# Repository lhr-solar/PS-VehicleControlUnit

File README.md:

# VehicleControlUnit
Vehicle Control Unit (VCU) for the 2026 Longhorn Racing Solar car

## Getting Started

### Cloning
Clone this repository using the following command
``` sh
git clone git@github.com:lhr-solar/PS-VehicleControlUnit.git --recursive
```

### Installation
Follow the installation instructions for your specific platform, found [here](https://lhrsolar.org/Embedded-Sharepoint/Installation/).  

Additionally, install the [Arduino IDE](https://docs.arduino.cc/software/ide/)

## Command Usage

### Firmware build and flash

Firmware builds use [Embedded-Sharepoint](Firmware/Embedded-Sharepoint) from `Firmware/Makefile`. Enter the nix shell first, then run all commands from `Firmware/`.

By default, **`FIRMWARE_TYPE=app`**: the image is linked for the resident UART bootloader (application region at `0x08010000`, 512 KB part with 64 KB bootloader). Full protocol, one-time bootloader programming, and host scripts: [UART Bootloader](Firmware/Embedded-Sharepoint/docs/UartBootloader.md). USART3 on PC10/PC11 matches the default bootloader UART on STM32G473.

**Nix shell (repository root):**

```sh
chmod +x ./run_nix.sh   # first time only
./run_nix.sh
cd Firmware
```

**Clean** (removes both `Firmware/build` and `Firmware/build/app`):

```sh
make clean
```

**Bootloader application (default)** — output under `Firmware/build/app`:

```sh
make
make flash
make flash-uart
```

**Standalone firmware** at `0x08000000` (no resident bootloader) — output under `Firmware/build`:

```sh
make clean
make FIRMWARE_TYPE=firmware
make flash FIRMWARE_TYPE=firmware
make flash-uart FIRMWARE_TYPE=firmware
```

When switching between `app` and `firmware`, run **`make clean`** first so linker maps and objects stay consistent.

**Other makefile variables:**

```sh
make PROJECT_TARGET=stm32g473xx    # default; override if you change MCU port
make NODAWG=1                      # optional macro for this repo
```

### Compiling tests

Tests live in `Firmware/tests/` and must be named `test_<name>.c`; the `test_` prefix and `.c` suffix are omitted from `TEST`.

```sh
make TEST=<name>
```

Example (`Firmware/tests/blinky_test.c`):

```sh
make TEST=blinky
make flash
```

To build a test image as standalone instead of the default bootloader app:

```sh
make clean
make TEST=blinky FIRMWARE_TYPE=firmware
make flash FIRMWARE_TYPE=firmware
```

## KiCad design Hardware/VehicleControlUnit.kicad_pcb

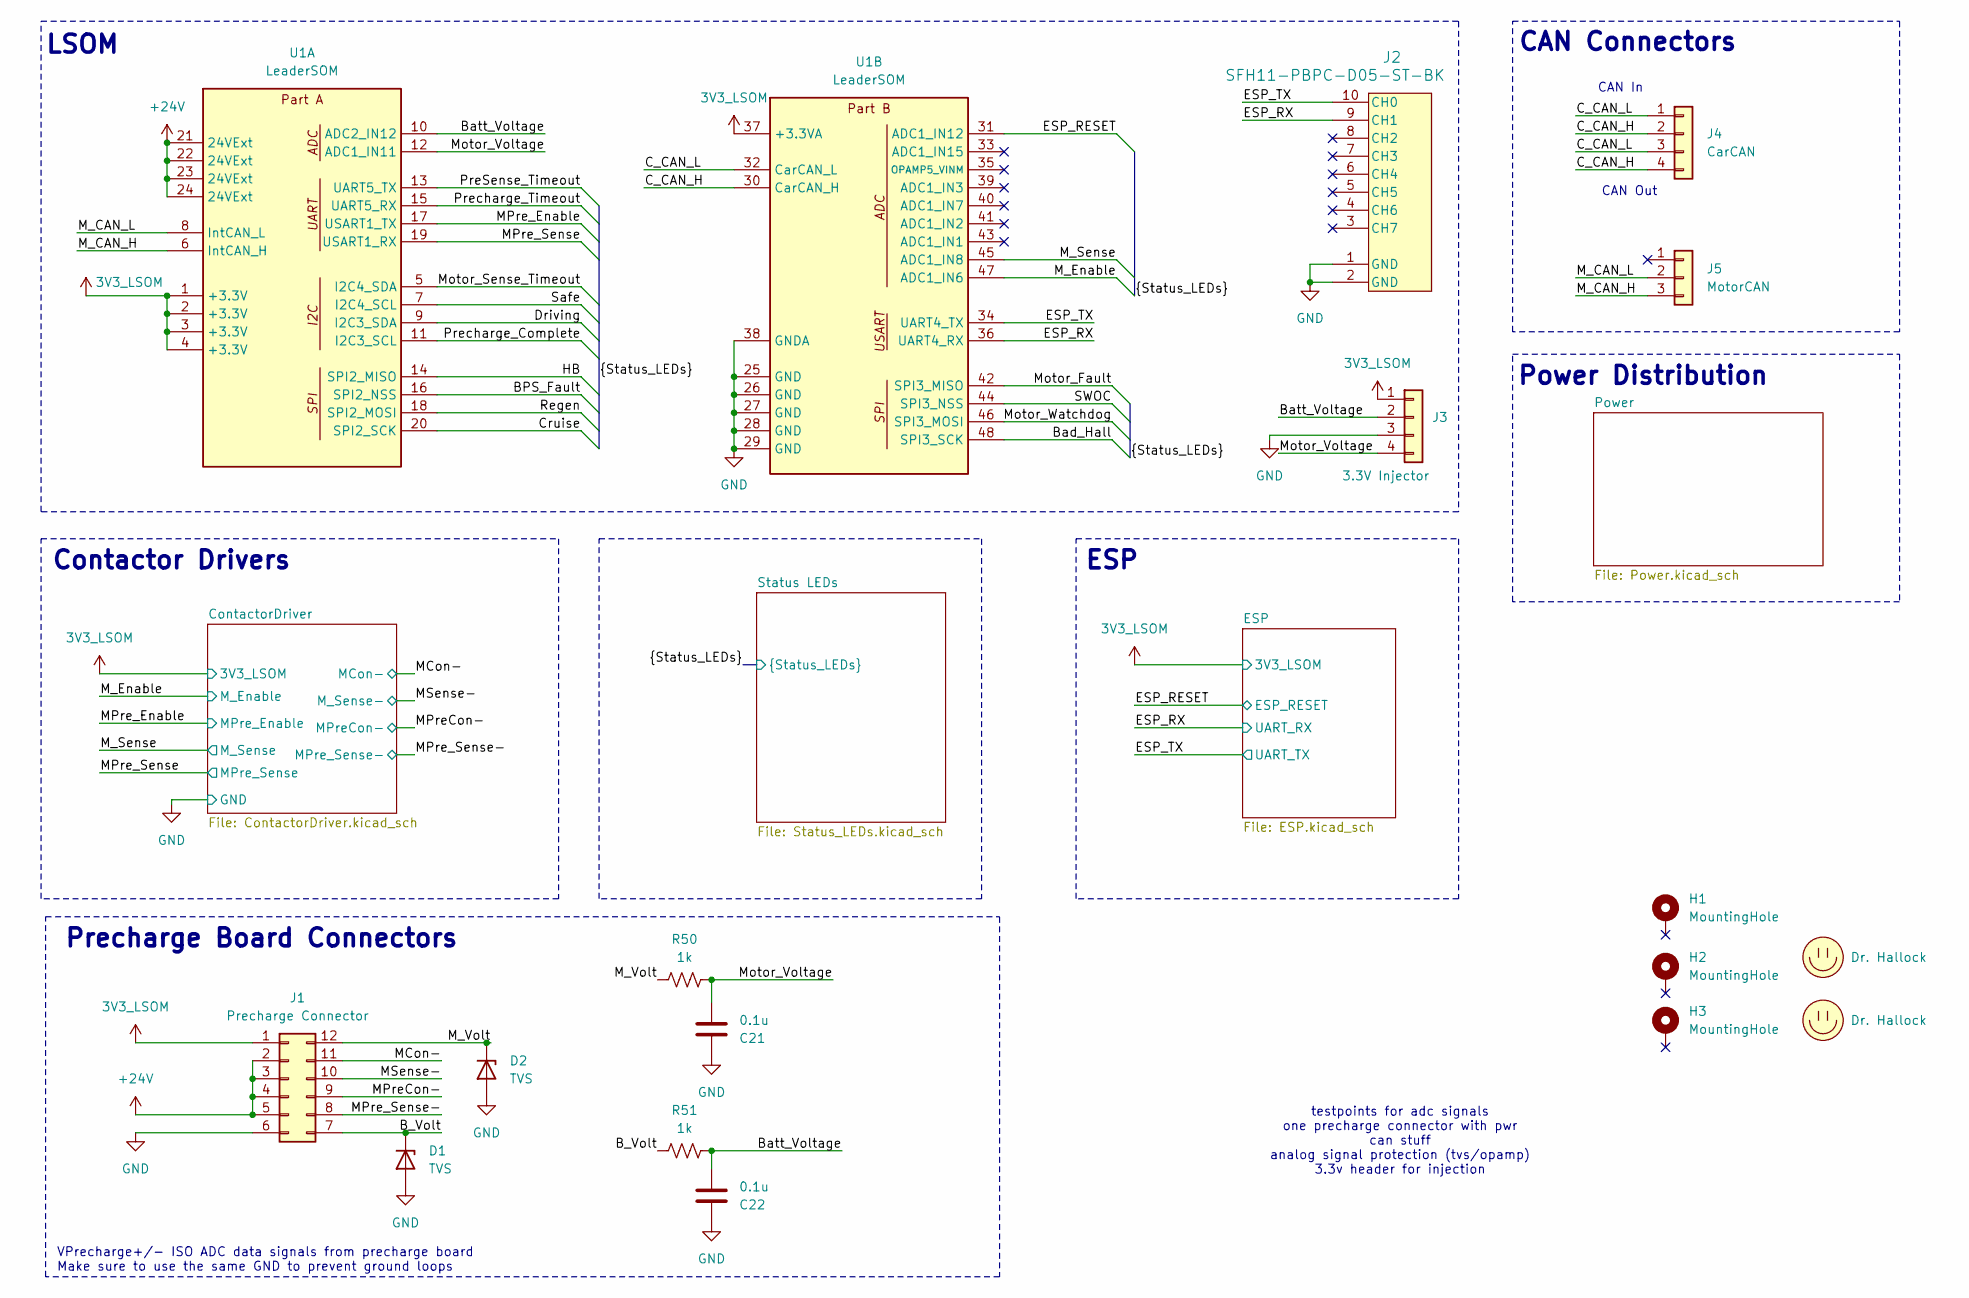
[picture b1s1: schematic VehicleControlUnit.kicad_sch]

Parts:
C21, C22: 0.1u; C_0603_1608Metric_Pad1.08x0.95mm_HandSolder; Mouser Part Number 963-HMK107B7104KA-T
D1, D2: TVS; D_SOD-123F; Mouser Part Number 576-SMF3.3
H1, H2, H3: MountingHole; MountingHole_3.2mm_M3_Pad_TopBottom
J1: Precharge Connector; Molex_Nano-Fit_105310-xx12_2x06_P2.50mm_Vertical; Mouser Part Number 538-105310-1112
J2: SFH11-PBPC-D05-ST-BK; CONN_SFH11-xxxC-D05-ST-XX_SUL
J3: 3.3V Injector; PinHeader_1x04_P2.54mm_Vertical
J4: CarCAN; Molex_Nano-Fit_105309-xx04_1x04_P2.50mm_Vertical; Mouser Part Number 538-105309-1104
J5: MotorCAN; Molex_Nano-Fit_105309-xx03_1x03_P2.50mm_Vertical; Mouser Part Number 538-105309-1103
LOGO1: Dr. Hallock; Hallock_Image_Tiny
LOGO2: Dr. Hallock; LHRs_LOGO
R50, R51: 1k; R_0603_1608Metric_Pad0.98x0.95mm_HandSolder; Mouser Part Number 71-CRCW06031K00FKEI
U1: LeaderSOM

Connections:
3V3_LSOM: J1.1, J3.1, U1.1 (+3.3V), U1.2 (+3.3V), U1.3 (+3.3V), U1.4 (+3.3V), U1.37 (+3.3VA); also elsewhere on the board
+24V: J1.2, J1.3, J1.4, J1.5, U1.21 (24VExt), U1.22 (24VExt), U1.23 (24VExt), U1.24 (24VExt); also elsewhere on the board
/BPS_Fault: U1.16 (SPI2_NSS); also elsewhere on the board
/B_Volt: D1.1 (K), J1.7, R51.2
/Bad_Hall: U1.48 (SPI3_SCK); also elsewhere on the board
/Batt_Voltage: C22.2, J3.2, R51.1, U1.10 (ADC2_IN12)
/C_CAN_H: J4.2, J4.4, U1.30 (CarCAN_H)
/C_CAN_L: J4.1, J4.3, U1.32 (CarCAN_L)
/Cruise: U1.20 (SPI2_SCK); also elsewhere on the board
/Driving: U1.9 (I2C3_SDA); also elsewhere on the board
/ESP_RESET: U1.31 (ADC1_IN12); also elsewhere on the board
/ESP_RX: J2.9 (CH1), U1.36 (UART4_RX); also elsewhere on the board
/ESP_TX: J2.10 (CH0), U1.34 (UART4_TX); also elsewhere on the board
/HB: U1.14 (SPI2_MISO); also elsewhere on the board
/MCon-: J1.11; also elsewhere on the board
/MPreCon-: J1.9; also elsewhere on the board
/MPre_Enable: U1.17 (USART1_TX); also elsewhere on the board
/MPre_Sense: U1.19 (USART1_RX); also elsewhere on the board
/MPre_Sense-: J1.8; also elsewhere on the board
/MSense-: J1.10; also elsewhere on the board
/M_CAN_H: J5.3, U1.6 (IntCAN_H)
/M_CAN_L: J5.2, U1.8 (IntCAN_L)
/M_Enable: U1.47 (ADC1_IN6); also elsewhere on the board
/M_Sense: U1.45 (ADC1_IN8); also elsewhere on the board
/M_Volt: D2.1 (K), J1.12, R50.2
/Motor_Fault: U1.42 (SPI3_MISO); also elsewhere on the board
/Motor_Sense_Timeout: U1.5 (I2C4_SDA); also elsewhere on the board
/Motor_Voltage: C21.2, J3.4, R50.1, U1.12 (ADC1_IN11)
/Motor_Watchdog: U1.46 (SPI3_MOSI); also elsewhere on the board
/PreSense_Timeout: U1.13 (UART5_TX); also elsewhere on the board
/Precharge_Complete: U1.11 (I2C3_SCL); also elsewhere on the board
/Precharge_Timeout: U1.15 (UART5_RX); also elsewhere on the board
/Regen: U1.18 (SPI2_MOSI); also elsewhere on the board
/SWOC: U1.44 (SPI3_NSS); also elsewhere on the board
/Safe: U1.7 (I2C4_SCL); also elsewhere on the board
GND: C21.1, C22.1, D1.2 (A), D2.2 (A), J1.6, J2.1 (GND), J2.2 (GND), J3.3, U1.25 (GND), U1.26 (GND), U1.27 (GND), U1.28 (GND), U1.29 (GND), U1.38 (GNDA); also elsewhere on the board

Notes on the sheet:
Precharge Board Connectors
CAN In
Contactor Drivers
testpoints for adc signals one precharge connector with pwr can stuff analog signal protection (tvs/opamp) 3.3v header for injection
Power Distribution
VPrecharge+/- ISO ADC data signals from precharge board Make sure to use the same GND to prevent ground loops
LSOM
ESP
CAN Out
CAN Connectors

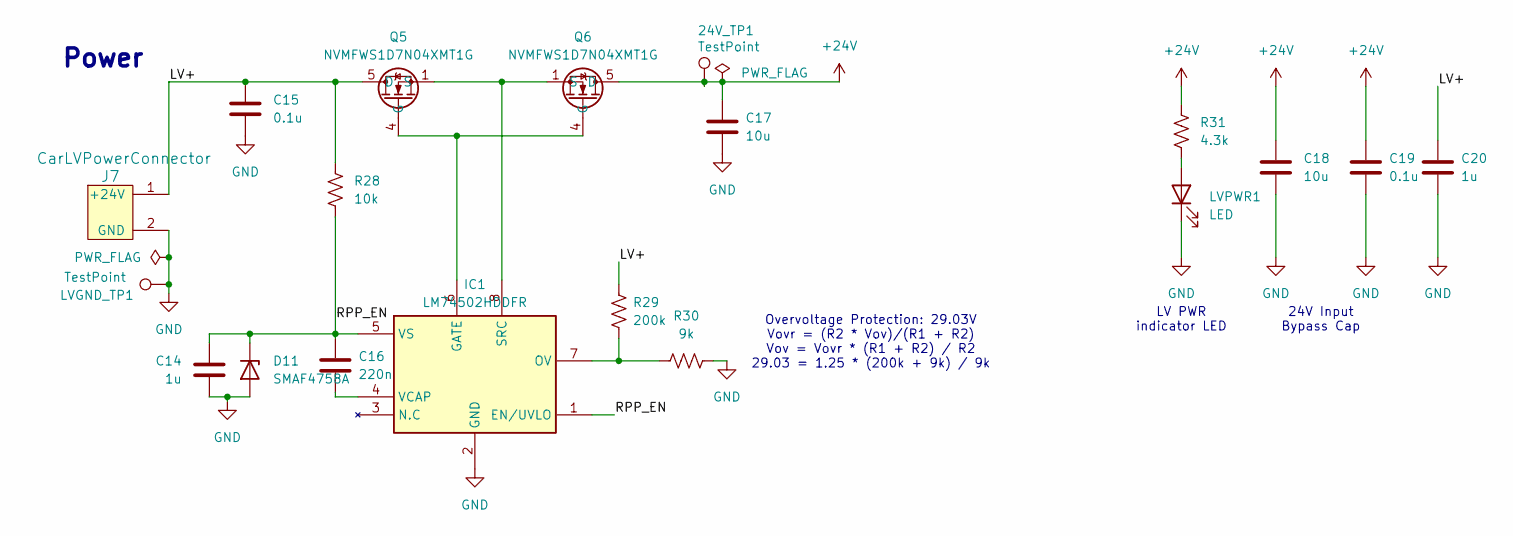
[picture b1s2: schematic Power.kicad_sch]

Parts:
24V_TP1: TestPoint; TestPoint_Keystone_5005-5009_Compact
C14: 1u; C_0603_1608Metric_Pad1.08x0.95mm_HandSolder; Mouser Part Number 963-UMK107BJ105KA-T
C15, C19: 0.1u; C_0603_1608Metric_Pad1.08x0.95mm_HandSolder; Mouser Part Number 963-HMK107B7104KA-T
C16: 220n; C_0603_1608Metric_Pad1.08x0.95mm_HandSolder; Mouser Part Number 963-MSASU168SB7224KT
C17, C18: 10u; C_0805_2012Metric_Pad1.18x1.45mm_HandSolder; Mouser Part Number 81-GRM21BR61H106KE3K
C20: 1u; C_0603_1608Metric_Pad1.08x0.95mm_HandSolder; Mouser Part Number 963-HMK107B7104KA-T
D11: SMAF4758A; SODFL5026X125N
IC1: LM74502HDDFR; SOT65P280X110-8N; Mouser Part Number 595-LM74502HDDFR
J7: CarLVPowerConnector; Molex_Nano-Fit_105309-xx02_1x02_P2.50mm_Vertical; Mouser Part Number 538-105309-1102
LVGND_TP1: TestPoint; TestPoint_Keystone_5005-5009_Compact
LVPWR1: LED; LED_0603_1608Metric_Pad1.05x0.95mm_HandSolder
Q5, Q6: NVMFWS1D7N04XMT1G; NVMFWS3D0P04M8LT1G
R28: 10k; R_0603_1608Metric_Pad0.98x0.95mm_HandSolder; Mouser Part Number 71-CRCW060310K0FKEI
R29: 200k; R_0603_1608Metric_Pad0.98x0.95mm_HandSolder; Mouser Part Number 594-MCT06030C2003FP5
R30: 9k; R_0603_1608Metric_Pad0.98x0.95mm_HandSolder; Mouser Part Number 594-MCT06030C9091FP5
R31: 4.3k; R_0603_1608Metric_Pad0.98x0.95mm_HandSolder; Mouser Part Number 71-CRCW0603-4.3K-E3

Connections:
+24V: 24V_TP1.1, C17.1, C18.1, C19.1, Q6.5 (D), Q6.6 (D), Q6.7 (D), Q6.8 (D), Q6.9 (D), R31.1; also elsewhere on the board
/Power/LV+: C15.1, C20.1, J7.1 (+24V), Q5.5 (D), Q5.6 (D), Q5.7 (D), Q5.8 (D), Q5.9 (D), R28.1, R29.1
/Power/RPP_EN: C14.2, C16.1, D11.1 (K), IC1.1 (EN/UVLO), IC1.5 (VS), R28.2
GND: C14.1, C15.2, C17.2, C18.2, C19.2, C20.2, D11.2 (A), IC1.2 (GND), J7.2 (GND), LVGND_TP1.1, LVPWR1.1 (K), R30.2; also elsewhere on the board
unnamed: IC1.6 (GATE), Q5.4 (G), Q6.4 (G)
unnamed: IC1.7 (OV), R29.2, R30.1
unnamed: IC1.8 (SRC), Q5.1 (S), Q5.2 (S), Q5.3 (S), Q6.1 (S), Q6.2 (S), Q6.3 (S)
unnamed: C16.2, IC1.4 (VCAP)
unnamed: LVPWR1.2 (A), R31.2

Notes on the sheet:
Overvoltage Protection: 29.03V Vovr = (R2 * Vov)/(R1 + R2) Vov = Vovr * (R1 + R2) / R2 29.03 = 1.25 * (200k + 9k) / 9k
LV PWR indicator LED
24V Input Bypass Cap
Power

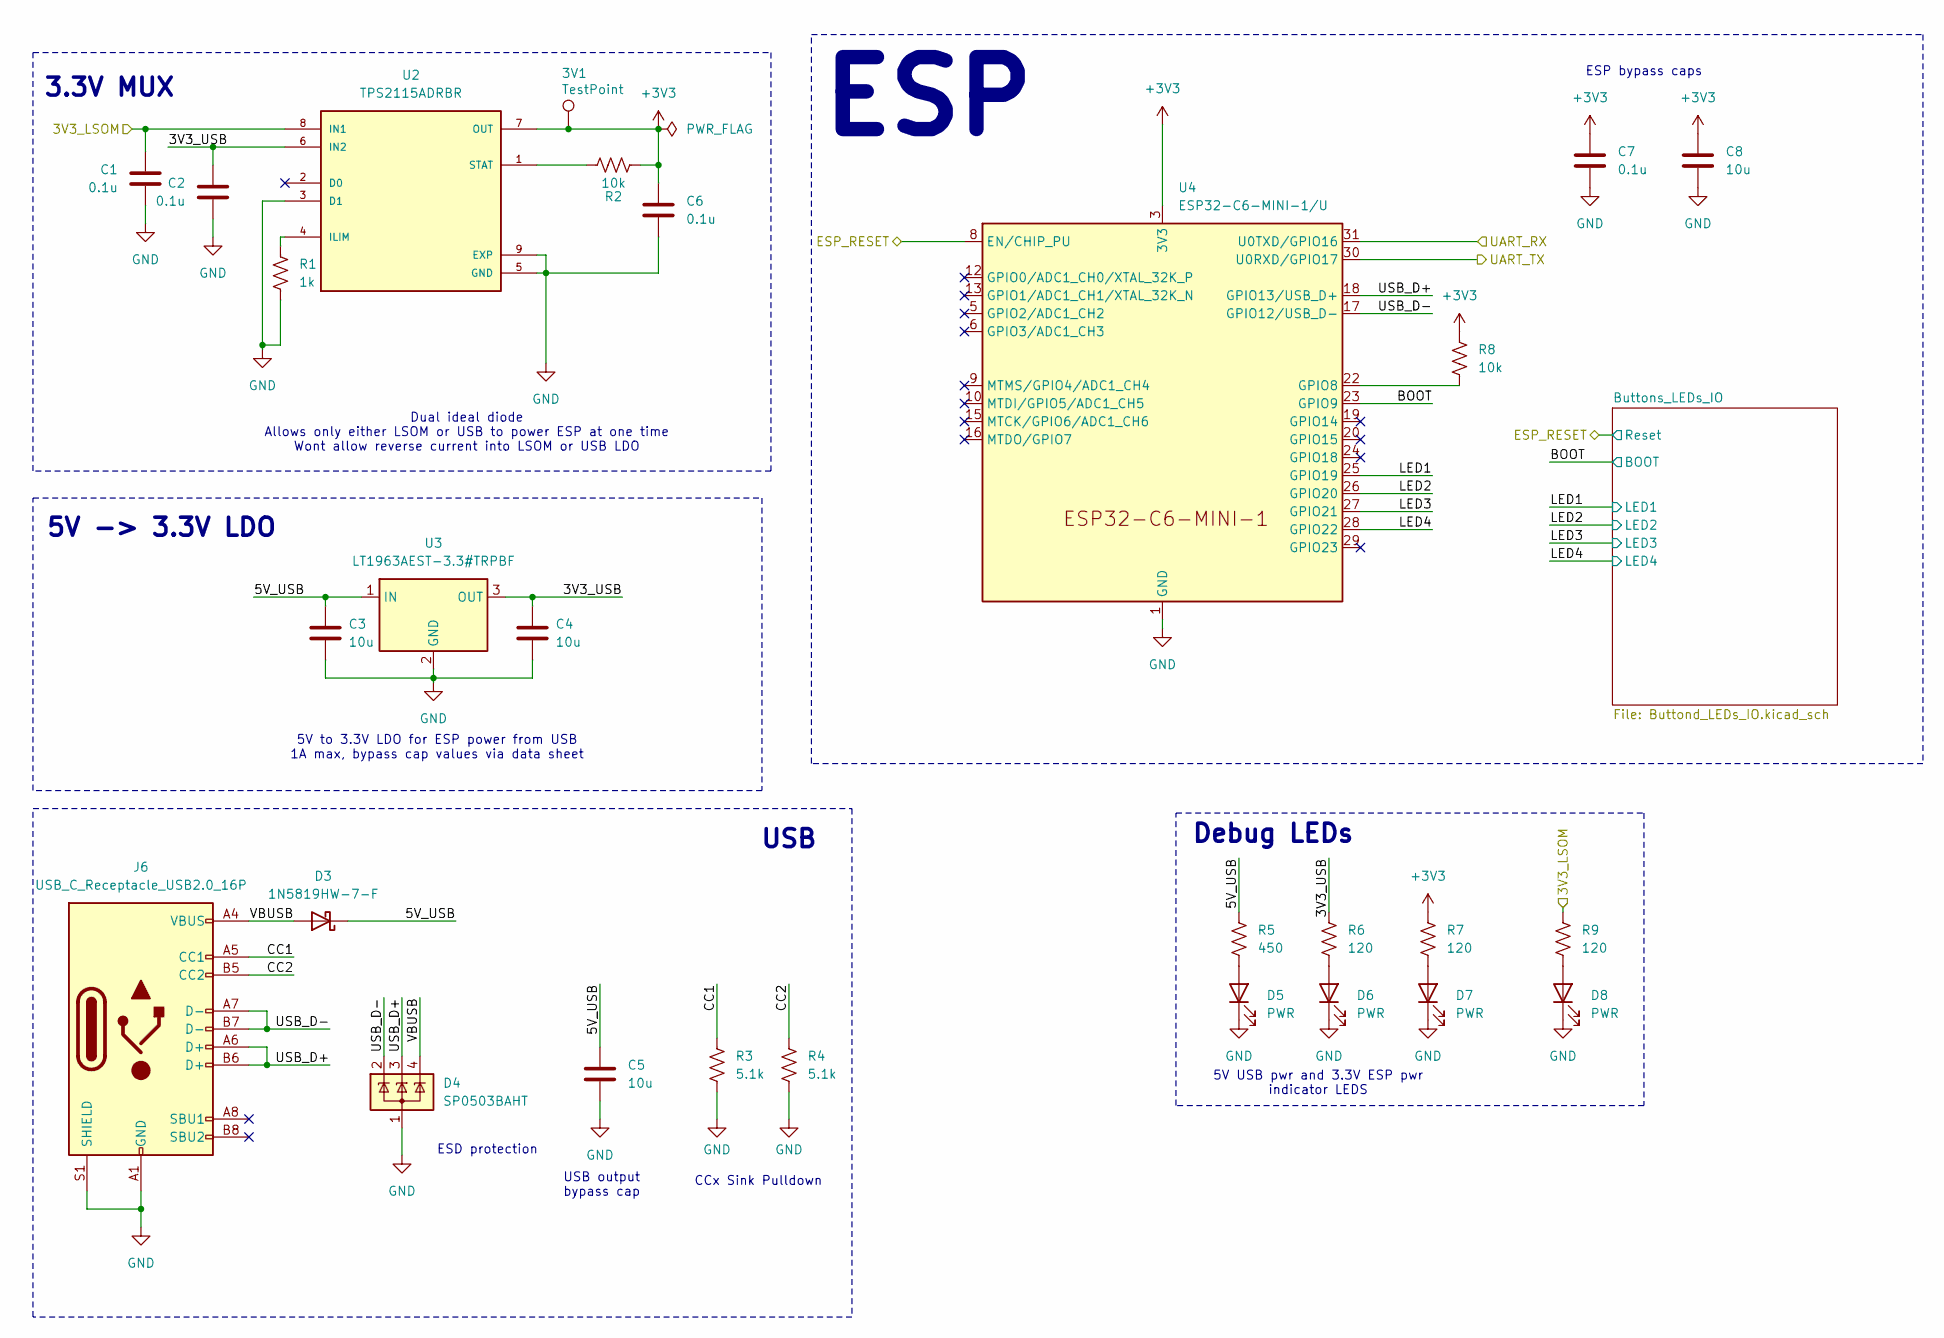
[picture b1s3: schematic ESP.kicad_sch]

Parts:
3V1: TestPoint; TestPoint_Keystone_5005-5009_Compact
C1, C2, C6, C7: 0.1u; C_0603_1608Metric_Pad1.08x0.95mm_HandSolder; Mouser Part Number 963-HMK107B7104KA-T
C3, C4, C5, C8: 10u; C_0805_2012Metric_Pad1.18x1.45mm_HandSolder; Mouser Part Number 81-GRM21BR61H106KE3K
D3: 1N5819HW-7-F; D_SOD-123; Mouser Part Number 621-1N5819HW-F
D4: SP0503BAHT; SOT-143; Mouser Part Number 576-SP0503BAHTG
D5, D6, D7, D8: PWR; LED_0603_1608Metric_Pad1.05x0.95mm_HandSolder
J6: USB_C_Receptacle_USB2.0_16P; USB_C_Receptacle_GCT_USB4105-xx-A_16P_TopMnt_Horizontal; Mouser Part Number 640-USB4215-03-A
R1: 1k; R_0603_1608Metric_Pad0.98x0.95mm_HandSolder; Mouser Part Number 71-CRCW06031K00FKEI
R2, R8: 10k; R_0603_1608Metric_Pad0.98x0.95mm_HandSolder; Mouser Part Number 71-CRCW060310K0FKEI
R3, R4: 5.1k; R_0603_1608Metric_Pad0.98x0.95mm_HandSolder; Mouser Part Number 71-CRCW06035K10FKEC
R5: 450; R_0603_1608Metric_Pad0.98x0.95mm_HandSolder; Mouser Part Number 71-CRCW1206-470-E3
R6, R7, R9: 120; R_0603_1608Metric_Pad0.98x0.95mm_HandSolder; Mouser Part Number 71-CRCW0603120RFKEC
U2: TPS2115ADRBR; SON65P300X300X100-9N; Mouser Part Number 595-TPS2115ADRBR
U3: LT1963AEST-3.3#TRPBF; SOT-223-3_TabPin2; Mouser Part Number 584-1963AEST-3.3TPF
U4: ESP32-C6-MINI-1/U; ESP32-C6-MINI-1; Mouser Part Number 356-ESP32-C6MINI1UN4

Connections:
3V3_LSOM: C1.1, R9.1, U2.8 (IN1); also elsewhere on the board
+3V3: 3V1.1, C6.1, C7.1, C8.1, R2.1, R7.1, R8.2, U2.7 (OUT), U4.3 (3V3); also elsewhere on the board
/ESP/3V3_USB: C2.1, C4.1, R6.1, U2.6 (IN2), U3.3 (OUT)
/ESP/5V_USB: C3.1, C5.1, D3.1 (K), R5.1, U3.1 (IN)
/ESP/BOOT: U4.23 (GPIO9); also elsewhere on the board
/ESP/CC1: J6.A5 (CC1), R3.1
/ESP/CC2: J6.B5 (CC2), R4.1
/ESP/LED1: U4.25 (GPIO19); also elsewhere on the board
/ESP/LED2: U4.26 (GPIO20); also elsewhere on the board
/ESP/LED3: U4.27 (GPIO21); also elsewhere on the board
/ESP/LED4: U4.28 (GPIO22); also elsewhere on the board
/ESP/USB_D+: D4.3 (K), J6.A6 (D+), J6.B6 (D+), U4.18 (GPIO13/USB_D+)
/ESP/USB_D-: D4.2 (K), J6.A7 (D-), J6.B7 (D-), U4.17 (GPIO12/USB_D-)
/ESP/VBUSB: D3.2 (A), D4.4 (K), J6.A4 (VBUS), J6.A9 (VBUS), J6.B4 (VBUS), J6.B9 (VBUS)
/ESP_RESET: U4.8 (EN/CHIP_PU); also elsewhere on the board
/ESP_RX: U4.31 (U0TXD/GPIO16); also elsewhere on the board
/ESP_TX: U4.30 (U0RXD/GPIO17); also elsewhere on the board
GND: C1.2, C2.2, C3.2, C4.2, C5.2, C6.2, C7.2, C8.2, D4.1 (A), D5.1 (K), D6.1 (K), D7.1 (K), D8.1 (K), J6.A1 (GND), J6.A12 (GND), J6.B1 (GND), J6.B12 (GND), J6.S1 (SHIELD), J6.S2 (Shield), J6.S3 (Shield), J6.S4 (Shield), R1.2, R3.2, R4.2, U2.3 (D1), U2.5 (GND), U2.9 (EXP), U3.2 (GND), U4.1 (GND), U4.2 (GND), U4.11 (GND), U4.14 (GND), U4.36 (GND), U4.37 (GND), U4.38 (GND), U4.39 (GND), U4.40 (GND), U4.41 (GND), U4.42 (GND), U4.43 (GND), U4.44 (GND), U4.45 (GND), U4.46 (GND), U4.47 (GND), U4.48 (GND), U4.49 (GND), U4.50 (GND), U4.51 (GND), U4.52 (GND), U4.53 (GND); also elsewhere on the board
unnamed: D5.2 (A), R5.2
unnamed: D6.2 (A), R6.2
unnamed: D7.2 (A), R7.2
unnamed: D8.2 (A), R9.2
unnamed: R1.1, U2.4 (ILIM)
unnamed: R2.2, U2.1 (STAT)
unnamed: R8.1, U4.22 (GPIO8)

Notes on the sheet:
3.3V MUX
Dual ideal diode Allows only either LSOM or USB to power ESP at one time Wont allow reverse current into LSOM or USB LDO
5V USB pwr and 3.3V ESP pwr indicator LEDS
USB output bypass cap
ESP
ESD protection
CCx Sink Pulldown
5V -> 3.3V LDO
USB
ESP bypass caps
5V to 3.3V LDO for ESP power from USB 1A max, bypass cap values via data sheet
Debug LEDs

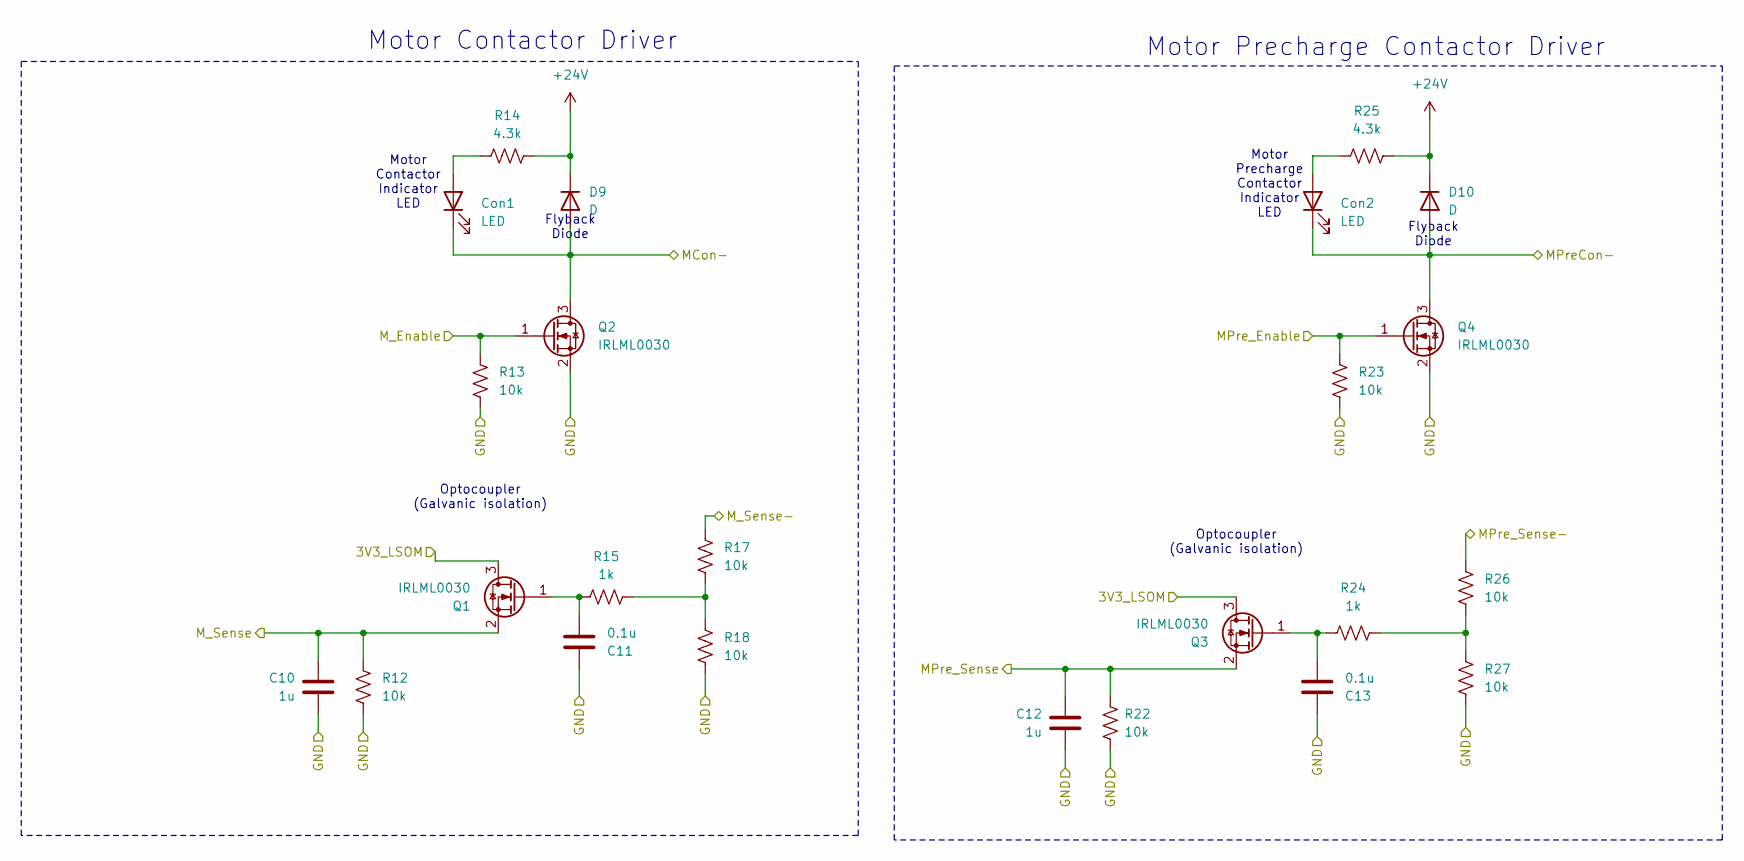
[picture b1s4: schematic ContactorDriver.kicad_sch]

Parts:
C10, C12: 1u; C_0603_1608Metric_Pad1.08x0.95mm_HandSolder; Mouser Part Number 963-UMK107BJ105KA-T
C11, C13: 0.1u; C_0603_1608Metric_Pad1.08x0.95mm_HandSolder; Mouser Part Number 963-HMK107B7104KA-T
Con1, Con2: LED; LED_0603_1608Metric_Pad1.05x0.95mm_HandSolder
D9, D10: D; SODFL4724X108N; Mouser Part Number 78-VSSAF510HM3/H
Q1, Q2, Q3, Q4: IRLML0030; SOT-23; Mouser Part Number 942-IRLML0030TRPBF
R12, R13, R22, R23: 10k; R_0603_1608Metric_Pad0.98x0.95mm_HandSolder; Mouser Part Number 71-CRCW060310K0FKEI
R14, R25: 4.3k; R_0603_1608Metric_Pad0.98x0.95mm_HandSolder; Mouser Part Number 71-CRCW0603-4.3K-E3
R15, R24: 1k; R_0603_1608Metric_Pad0.98x0.95mm_HandSolder; Mouser Part Number 71-CRCW06031K00FKEI
R17, R18, R26, R27: 10k; R_0603_1608Metric_Pad0.98x0.95mm_HandSolder; Mouser Part Number 71-CRCW06031K00FKEI

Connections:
3V3_LSOM: Q1.3 (D), Q3.3 (D); also elsewhere on the board
+24V: D9.1 (K), D10.1 (K), R14.2, R25.2; also elsewhere on the board
/MCon-: Con1.1 (K), D9.2 (A), Q2.3 (D); also elsewhere on the board
/MPreCon-: Con2.1 (K), D10.2 (A), Q4.3 (D); also elsewhere on the board
/MPre_Enable: Q4.1 (G), R23.1; also elsewhere on the board
/MPre_Sense: C12.2, Q3.2 (S), R22.1; also elsewhere on the board
/MPre_Sense-: R26.1; also elsewhere on the board
/MSense-: R17.1; also elsewhere on the board
/M_Enable: Q2.1 (G), R13.1; also elsewhere on the board
/M_Sense: C10.2, Q1.2 (S), R12.1; also elsewhere on the board
GND: C10.1, C11.1, C12.1, C13.1, Q2.2 (S), Q4.2 (S), R12.2, R13.2, R18.2, R22.2, R23.2, R27.2; also elsewhere on the board
unnamed: Con1.2 (A), R14.1
unnamed: Con2.2 (A), R25.1
unnamed: C11.2, Q1.1 (G), R15.2
unnamed: C13.2, Q3.1 (G), R24.2
unnamed: R15.1, R17.2, R18.1
unnamed: R24.1, R26.2, R27.1

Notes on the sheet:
Motor Precharge Contactor Driver
Optocoupler (Galvanic isolation)
Motor Contactor Indicator LED
Motor Contactor Driver
Flyback Diode
Motor Precharge Contactor Indicator LED

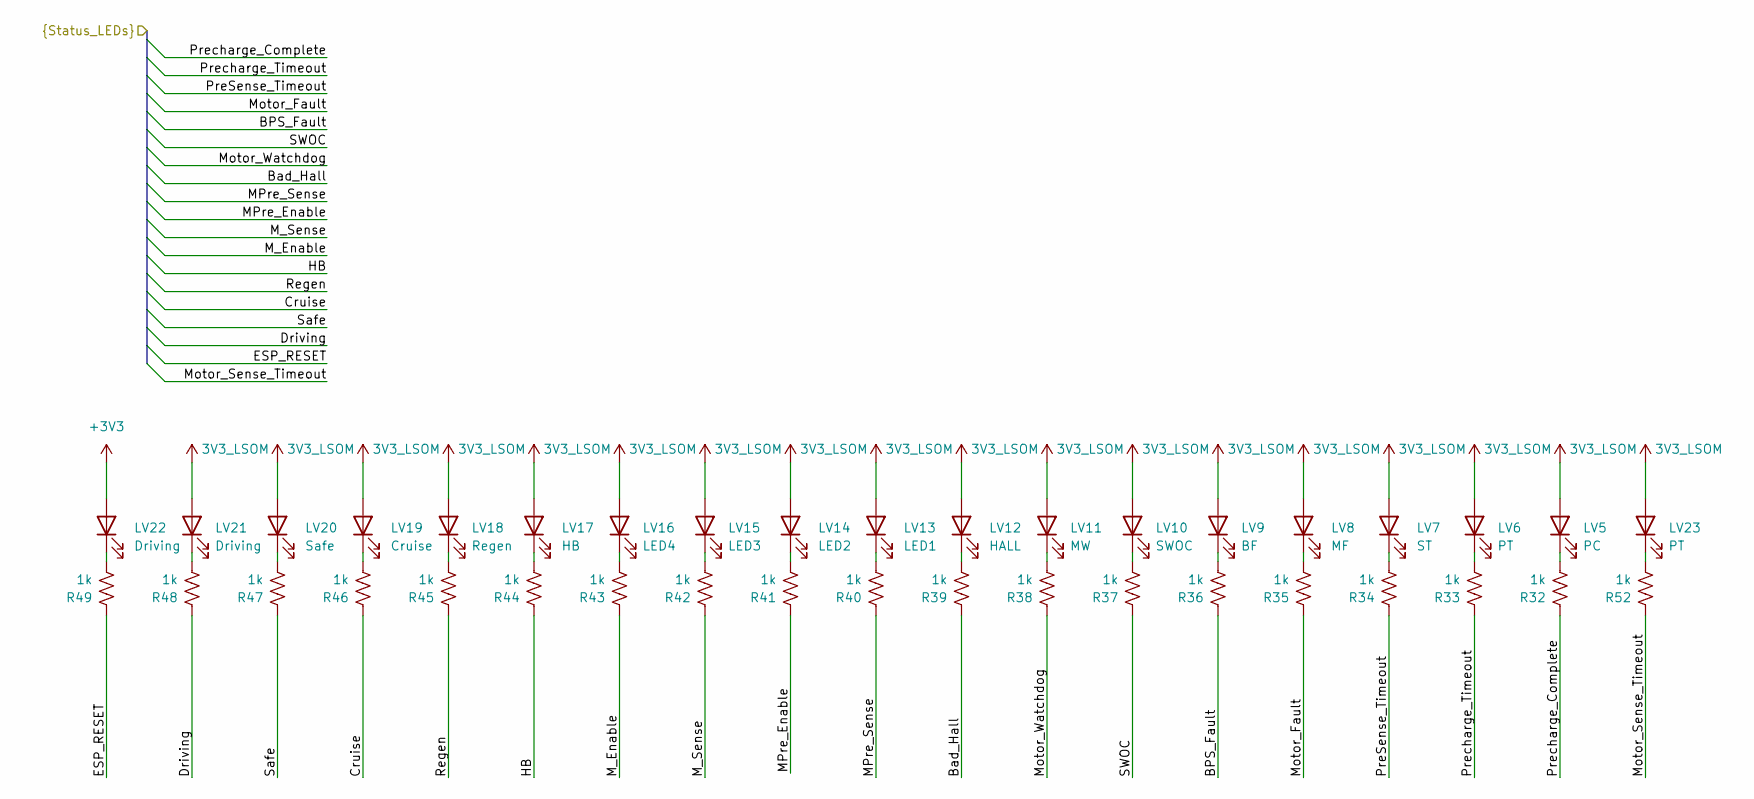
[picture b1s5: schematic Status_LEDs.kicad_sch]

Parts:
LV5: PC; LED_0603_1608Metric_Pad1.05x0.95mm_HandSolder
LV6, LV23: PT; LED_0603_1608Metric_Pad1.05x0.95mm_HandSolder
LV7: ST; LED_0603_1608Metric_Pad1.05x0.95mm_HandSolder
LV8: MF; LED_0603_1608Metric_Pad1.05x0.95mm_HandSolder
LV9: BF; LED_0603_1608Metric_Pad1.05x0.95mm_HandSolder
LV10: SWOC; LED_0603_1608Metric_Pad1.05x0.95mm_HandSolder
LV11: MW; LED_0603_1608Metric_Pad1.05x0.95mm_HandSolder
LV12: HALL; LED_0603_1608Metric_Pad1.05x0.95mm_HandSolder
LV13: LED1; LED_0603_1608Metric_Pad1.05x0.95mm_HandSolder
LV14: LED2; LED_0603_1608Metric_Pad1.05x0.95mm_HandSolder
LV15: LED3; LED_0603_1608Metric_Pad1.05x0.95mm_HandSolder
LV16: LED4; LED_0603_1608Metric_Pad1.05x0.95mm_HandSolder
LV17: HB; LED_0603_1608Metric_Pad1.05x0.95mm_HandSolder
LV18: Regen; LED_0603_1608Metric_Pad1.05x0.95mm_HandSolder
LV19: Cruise; LED_0603_1608Metric_Pad1.05x0.95mm_HandSolder
LV20: Safe; LED_0603_1608Metric_Pad1.05x0.95mm_HandSolder
LV21, LV22: Driving; LED_0603_1608Metric_Pad1.05x0.95mm_HandSolder
R32, R33, R34, R35, R36, R37, R38, R39, R40, R41, R42, R43, R44, R45, R46, R47, R48, R49, R52: 1k; R_0603_1608Metric_Pad0.98x0.95mm_HandSolder; Mouser Part Number 71-CRCW0603120RFKEC

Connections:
3V3_LSOM: LV5.2 (A), LV6.2 (A), LV7.2 (A), LV8.2 (A), LV9.2 (A), LV10.2 (A), LV11.2 (A), LV12.2 (A), LV13.2 (A), LV14.2 (A), LV15.2 (A), LV16.2 (A), LV17.2 (A), LV18.2 (A), LV19.2 (A), LV20.2 (A), LV21.2 (A), LV23.2 (A); also elsewhere on the board
+3V3: LV22.2 (A); also elsewhere on the board
/BPS_Fault: R36.1; also elsewhere on the board
/Bad_Hall: R39.1; also elsewhere on the board
/Cruise: R46.1; also elsewhere on the board
/Driving: R48.1; also elsewhere on the board
/ESP_RESET: R49.1; also elsewhere on the board
/HB: R44.1; also elsewhere on the board
/MPre_Enable: R41.1; also elsewhere on the board
/MPre_Sense: R40.1; also elsewhere on the board
/M_Enable: R43.1; also elsewhere on the board
/M_Sense: R42.1; also elsewhere on the board
/Motor_Fault: R35.1; also elsewhere on the board
/Motor_Sense_Timeout: R52.1; also elsewhere on the board
/Motor_Watchdog: R38.1; also elsewhere on the board
/PreSense_Timeout: R34.1; also elsewhere on the board
/Precharge_Complete: R32.1; also elsewhere on the board
/Precharge_Timeout: R33.1; also elsewhere on the board
/Regen: R45.1; also elsewhere on the board
/SWOC: R37.1; also elsewhere on the board
/Safe: R47.1; also elsewhere on the board
unnamed: LV5.1 (K), R32.2
unnamed: LV6.1 (K), R33.2
unnamed: LV7.1 (K), R34.2
unnamed: LV8.1 (K), R35.2
unnamed: LV9.1 (K), R36.2
unnamed: LV10.1 (K), R37.2
unnamed: LV11.1 (K), R38.2
unnamed: LV12.1 (K), R39.2
unnamed: LV13.1 (K), R40.2
unnamed: LV14.1 (K), R41.2
unnamed: LV15.1 (K), R42.2
unnamed: LV16.1 (K), R43.2
unnamed: LV17.1 (K), R44.2
unnamed: LV18.1 (K), R45.2
unnamed: LV19.1 (K), R46.2
unnamed: LV20.1 (K), R47.2
unnamed: LV21.1 (K), R48.2
unnamed: LV22.1 (K), R49.2
unnamed: LV23.1 (K), R52.2

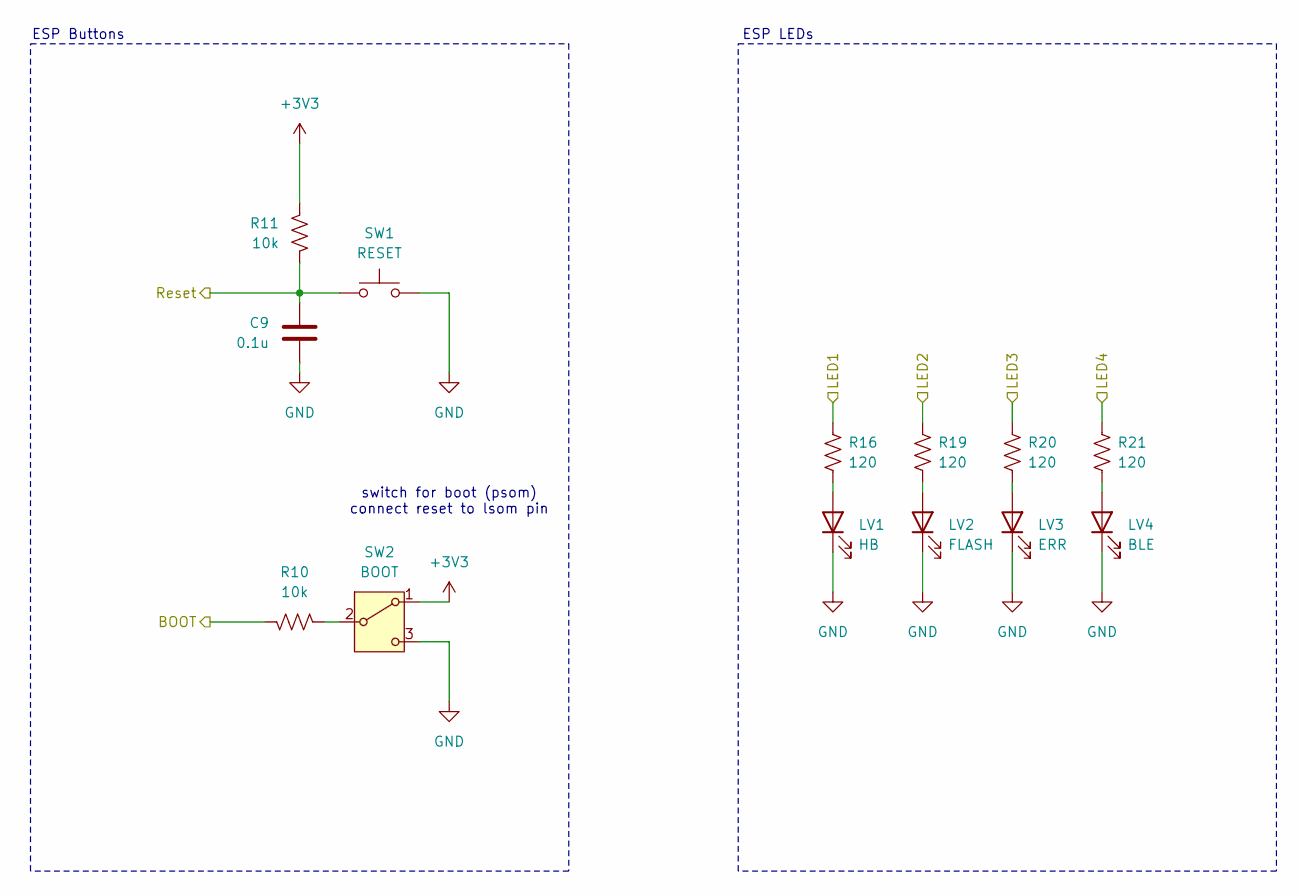
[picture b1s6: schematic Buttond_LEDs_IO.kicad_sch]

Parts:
C9: 0.1u; C_0603_1608Metric_Pad1.08x0.95mm_HandSolder; Mouser Part Number 963-HMK107B7104KA-T
LV1: HB; LED_0603_1608Metric_Pad1.05x0.95mm_HandSolder
LV2: FLASH; LED_0603_1608Metric_Pad1.05x0.95mm_HandSolder
LV3: ERR; LED_0603_1608Metric_Pad1.05x0.95mm_HandSolder
LV4: BLE; LED_0603_1608Metric_Pad1.05x0.95mm_HandSolder
R10, R11: 10k; R_0603_1608Metric_Pad0.98x0.95mm_HandSolder; Mouser Part Number 71-CRCW060310K0FKEI
R16, R19, R20, R21: 120; R_0603_1608Metric_Pad0.98x0.95mm_HandSolder; Mouser Part Number 71-CRCW0603120RFKEC
SW1: RESET; TL3365AF180QG; Mouser Part Number 667-EVQ-7Q203W
SW2: BOOT; SW_CJS-1200TA; Mouser Part Number 229-CJS-1200TA

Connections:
+3V3: R11.1, SW2.1 (A); also elsewhere on the board
/ESP/BOOT: R10.1; also elsewhere on the board
/ESP/LED1: R16.1; also elsewhere on the board
/ESP/LED2: R19.1; also elsewhere on the board
/ESP/LED3: R20.1; also elsewhere on the board
/ESP/LED4: R21.1; also elsewhere on the board
/ESP_RESET: C9.1, R11.2, SW1.3 (B), SW1.4 (B); also elsewhere on the board
GND: C9.2, LV1.1 (K), LV2.1 (K), LV3.1 (K), LV4.1 (K), SW1.1 (A), SW1.2 (A), SW2.3 (C); also elsewhere on the board
unnamed: LV1.2 (A), R16.2
unnamed: LV2.2 (A), R19.2
unnamed: LV3.2 (A), R20.2
unnamed: LV4.2 (A), R21.2
unnamed: R10.2, SW2.2 (B)

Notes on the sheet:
switch for boot (psom) connect reset to lsom pin
ESP Buttons
ESP LEDs

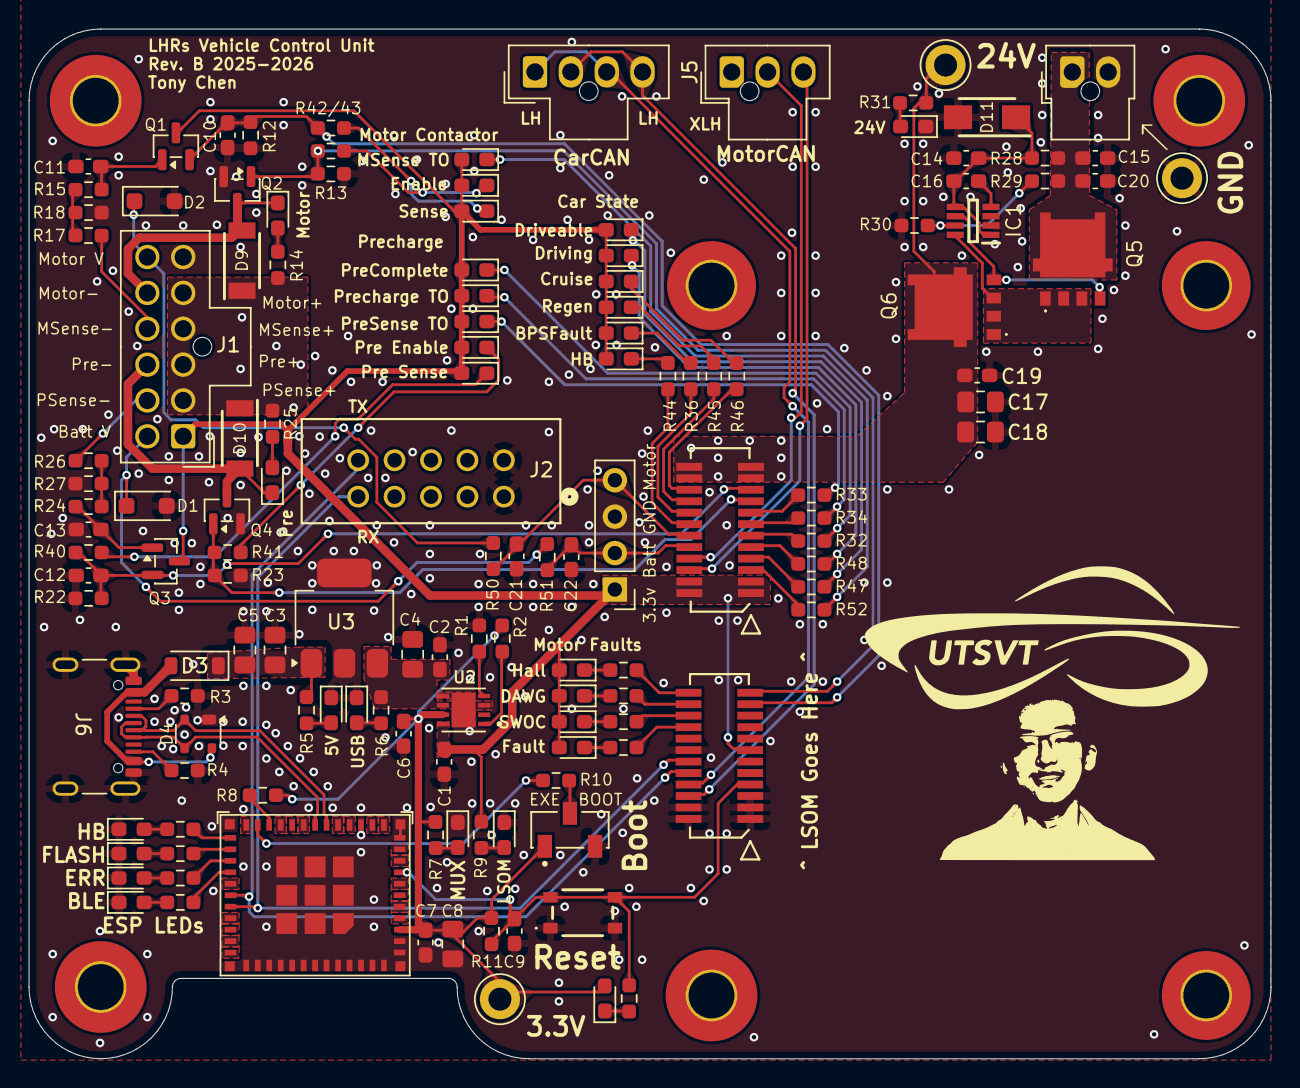
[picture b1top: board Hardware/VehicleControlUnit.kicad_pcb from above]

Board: 2 copper layers, 86.6 x 71.8 mm, 139 parts (1 on the bottom side), 93 nets.
